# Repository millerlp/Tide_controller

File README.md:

Tide_controller
===============

Arduino code and associated files for building an aquarium tide height controller. This assumes that you 
have downloaded and installed the latest version of the Arduino software (v1.6.4, or newer).

Installation:

To operate the tide controller rack, install the following:

1. Install a copy of RTClib in your Arduino/libraries/ directory. If there is not already a libraries directory, create it now. RTClib can be downloaded from https://github.com/millerlp/RTClib. If the copy you download and unzip is called "RTClib-master", rename the folder to simply be "RTClib".

2. Copy the folder with the tide library for your site (i.e. TidelibSanDiegoSanDiegoBay) into Arduino/libraries/

3. Copy the Tide_controller_v2_5 folder (or most recent version) into your Arduino folder where 
your other sketches are normally stored. 

4. Open the Tide_controller sketch in the Arduino IDE, and make sure the correct tide site
library is referenced in the Initial Setup section, near line 57, with a line like:

	\#include "TidelibSanDiegoSanDiegoBay.h"

That line should contain the name of the library for your local site that you copied into Arduino/libraries/.

5. If you want to change the tide range in which the tide rack travels, you can change the
value for the upperPos on or around line 64, which looks like:
	float upperPos = 5.0;
That line represents the upper limit at which the tide rack will stop moving upward, even
if the predicted tide goes higher. The units of upperPos are feet (not meters or inches). 

Plug the Arduino in to the computer using a USB cable. Upload the program to the Arduino. 
Open the serial monitor to view the output. See the http://arduino.cc site for help with 
these steps. 

------------------------------
If the real time clock attached to the Arduino is not yet set, you need to set it one time
before loading the tide prediction software onto the Arduino. Open the Arduino software and 
go to File>Examples>RTClib>settime_exact.ino. Follow the instructions at the top of
that sketch to upload the correct time to your real time clock. Make sure the time you enter
is in your local standard time, not Daylight Savings Time (which runs Mar-Nov
in most places). The tide prediction routine relies on the time being set to local 
standard time for your site, otherwise you won't get the current tide height out. After running
the settime_exact.ino sketch, before unplugging the Arduino, immediately upload a different 
sketch (such as the Tide_controller sketch) to the Arduino so that the clock doesn't try to reset 
itself repeatedly when the Arduino restarts.

-------------------------------
If there is no folder containing a tide prediction library for your desired site, it
will be necessary to generate a library using the R scripts found in the 
Generate_new_site_libraries directory. The harmonic data for NOAA sites are all in
the Harmonics_20120302.Rdata file. With these data, you can generate a new library
by running the R script tide_harmonics_library_generator.R. Inside that file, you must
enter a name for the site you're interested in on the line
stationID = 'Monterey Harbor'
Change the value inside the quote marks to match your site, save the file, and run the
script in R. It will create a new directory with the necessary library files inside that
can be copied into the Arduino/libraries/ folder. Find the name for your site by looking 
through the XTide website http://www.flaterco.com/xtide/locations.html 
XTide only produces harmonics for 635 reference tide stations (all others are approximated 
from these tide stations), so you need to find the nearest station listed as "Ref" on that 
page, rather than "Sub" stations.

The other R scripts in the Generate_new_site_libraries directory could be used to make an
updated Rdata file when XTide updates the original harmonics database and after you
convert it to a text file using the libtcd library from the XTide site (see the notes inside
the R scripts).

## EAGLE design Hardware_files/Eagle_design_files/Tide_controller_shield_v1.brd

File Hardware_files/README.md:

Tide_controller/Hardware_files

A add-on 'shield' designed to be used with an Arduino Uno was designed for this
project. The shield provides mounting points for the real time clock (DS3231),
buttons, indicator LEDs, resistors, and connectors to interface with the stepper 
motor controller and displays. 

See the file 'Tide_shield_notes.pdf' for more information on how this shield
is meant to be wired and used.

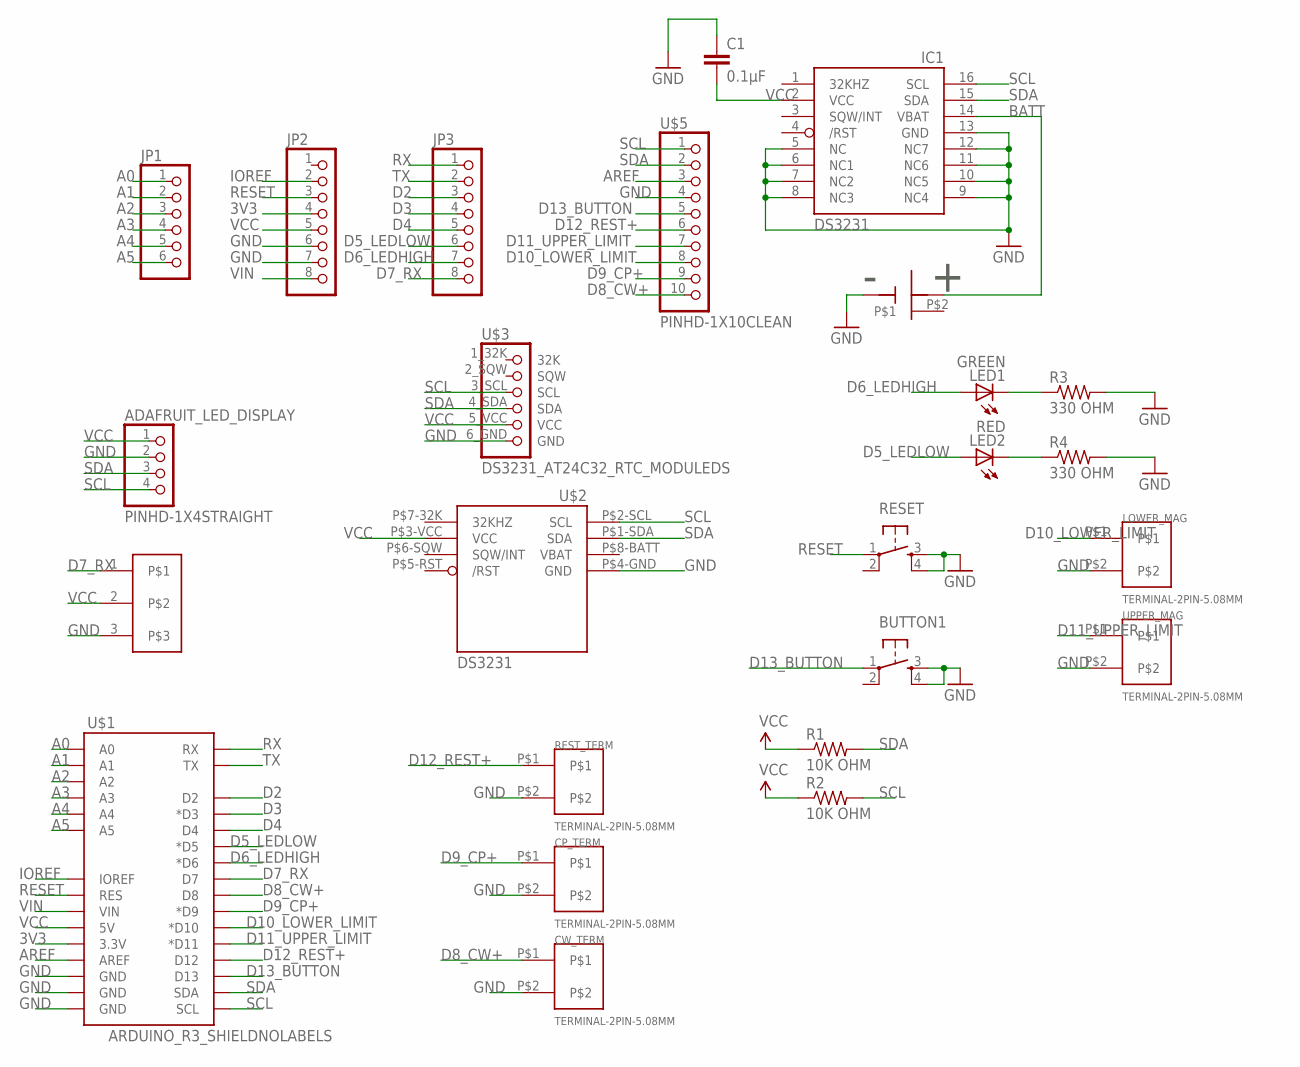
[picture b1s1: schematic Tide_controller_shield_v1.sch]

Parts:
ADAFRUIT_LED_DISPLAY: PINHD-1X4STRAIGHT; 1X04
BUTTON1: PUSHBUTTON-DPST-PTH; SWITCH-TACTILE-PTH-DPST
C1: 0.1µF; 0805
CP_TERM: TERMINAL-2PIN-5.08MM
CW_TERM: TERMINAL-2PIN-5.08MM
IC1: DS3231/SO; SO16W
JP1: PINHD-1X6CLEAN; 1X06-CLEAN
JP2, JP3: PINHD-1X8CLEANBIG; 1X08-CLEANBIG
LED1: GREEN; LED5MM
LED2: RED; LED5MM
LED_DISPLAY_SPARKFUN: PINHD-1X3; 1X03
LOWER_MAG: TERMINAL-2PIN-5.08MM
R1, R2: 10K OHM; 0309/10
R3, R4: 330 OHM; 0309/10
RESET: PUSHBUTTON-DPST-PTH; SWITCH-TACTILE-PTH-DPST
REST_TERM: TERMINAL-2PIN-5.08MM
U$1: ARDUINO_R3_SHIELDNOLABELS; UNO_R3_SHIELD_NOLABELS
U$2: CHRONODOT-OUTLINE
U$3: DS3231_AT24C32_RTC_MODULEDS; DS3231_AT24C32_RTC_MODULE
U$5: PINHD-1X10CLEAN; 1X10-CLEANBIG
U$6: CR1220_BATTERY_HOLDERSMD; CR1220_BATTERY_HOLDER_SMD
UPPER_MAG: TERMINAL-2PIN-5.08MM

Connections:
3V3: JP2.4, U$1.3.3V
A0: JP1.1, U$1.A0
A1: JP1.2, U$1.A1
A2: JP1.3, U$1.A2
A3: JP1.4, U$1.A3
A4: JP1.5, U$1.A4
A5: JP1.6, U$1.A5
AREF: U$1.AREF, U$5.3
BATT: IC1.14 (VBAT), U$6.P$1 (VBAT)
D2: JP3.3, U$1.D2
D3: JP3.4, U$1.D3 (*D3)
D4: JP3.5, U$1.D4
D5_LEDLOW: JP3.6, LED2.A, U$1.D5 (*D5)
D6_LEDHIGH: JP3.7, LED1.A, U$1.D6 (*D6)
D7_RX: JP3.8, LED_DISPLAY_SPARKFUN.1, U$1.D7
D8_CW+: CW_TERM.P$1, U$1.D8, U$5.10
D9_CP+: CP_TERM.P$1, U$1.D9 (*D9), U$5.9
D10_LOWER_LIMIT: LOWER_MAG.P$1, U$1.D10 (*D10), U$5.8
D11_UPPER_LIMIT: U$1.D11 (*D11), U$5.7, UPPER_MAG.P$1
D12_REST+: REST_TERM.P$1, U$1.D12, U$5.6
D13_BUTTON: BUTTON1.1, U$1.D13, U$5.5
GND: ADAFRUIT_LED_DISPLAY.2, BUTTON1.3, BUTTON1.4, C1.1, CP_TERM.P$2, CW_TERM.P$2, IC1.5 (NC), IC1.6 (NC1), IC1.7 (NC2), IC1.8 (NC3), IC1.9 (NC4), IC1.10 (NC5), IC1.11 (NC6), IC1.12 (NC7), IC1.13 (GND), JP2.6, JP2.7, LED_DISPLAY_SPARKFUN.3, LOWER_MAG.P$2, R3.2, R4.2, RESET.3, RESET.4, REST_TERM.P$2, U$1.GND@0 (GND), U$1.GND@1 (GND), U$1.GND@2 (GND), U$2.P$4-GND (GND), U$3.6_GND (GND), U$5.4, U$6.GND, UPPER_MAG.P$2
IOREF: JP2.2, U$1.IOREF
unnamed: LED1.K (C), R3.1
unnamed: LED2.K (C), R4.1
RESET: JP2.3, RESET.1, U$1.RES
RX: JP3.1, U$1.RX
SCL: ADAFRUIT_LED_DISPLAY.4, IC1.16 (SCL), R2.2, U$1.SCL, U$2.P$2-SCL (SCL), U$3.3_SCL (SCL), U$5.1
SDA: ADAFRUIT_LED_DISPLAY.3, IC1.15 (SDA), R1.2, U$1.SDA, U$2.P$1-SDA (SDA), U$3.4_SDA (SDA), U$5.2
TX: JP3.2, U$1.TX
VBAT: U$2.P$8-BATT (VBAT)
VCC: ADAFRUIT_LED_DISPLAY.1, C1.2, IC1.2 (VCC), JP2.5, LED_DISPLAY_SPARKFUN.2, R1.1, R2.1, U$1.5V, U$2.P$3-VCC (VCC), U$3.5_VCC (VCC)
VIN: JP2.8, U$1.VIN

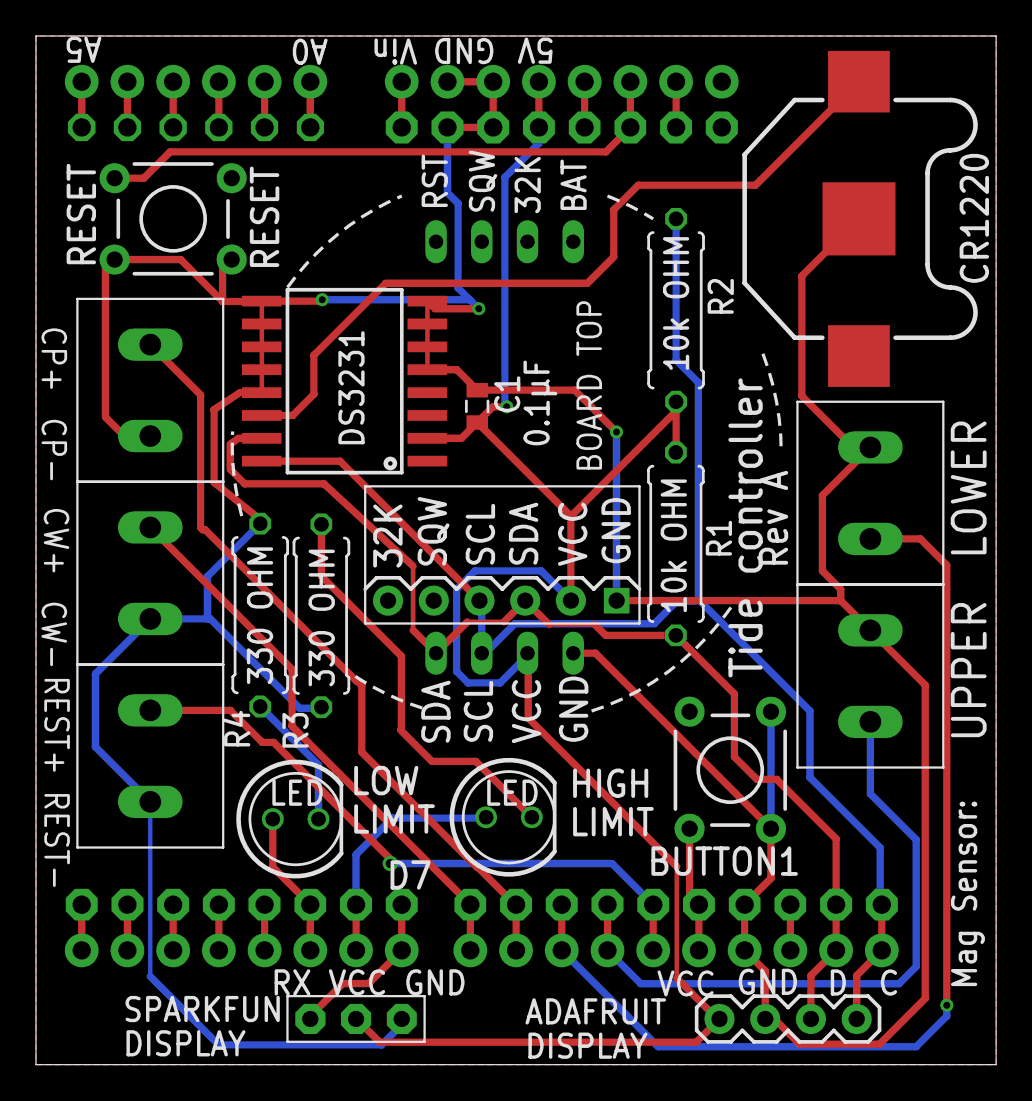
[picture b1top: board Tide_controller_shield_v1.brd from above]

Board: 2 copper layers, 53.3 x 57.1 mm, 25 parts (0 on the bottom side), 32 nets.

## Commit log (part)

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2012-05-03 Initial commit. Getting repository set up."
2012-05-03 GPL V3 license for the programs in this repository.
2012-05-03 This script contains two R functions for parsing a harmonics file from XTide.
2012-05-03 A script to extract data for a single tide station from the harmonics data generated by the tide_harmonics_parse.R script. This script outputs code to the command line that can be copied and pasted i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
2012-05-04 Initial commit of the Rdata file that can be read by the R script tide_extract_1site_harmonics.R. This Rdata file contains harmonics constituents for 637 reference tide stations from the NOAA databas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
2012-05-04 Added code to remove current speed stations from the harmonics data to reduce potential ambiguities in finding tide stations by name, since this code is only focused on predicting tide heights, not c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
2012-05-04 Still moving things around
2012-05-04 Changed output to send code to a text file that can be copy/pasted into the Arduino sketch. This creates code to initialize the various tide prediction arrays needed in the Arduino sketch.
2012-05-07 Started adding real time clock code, got sidetracked and instead switched to Motor_encoder_scratch2.ino. Updated setup instructions at bottom, PololuQik.h must also be modified, and the original Soft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
2012-05-07 Added code to calculate current year and hours since the start of current year.
2012-05-07 Added code to calculate current tide height once per minute. Need to check that timezone stuff is working still.
2012-05-08 First branch attempt
2012-05-09 First commit on this branch, no changes to .ino file
2012-05-09 Fixed duplication of values
2012-05-09 Added integer version of R script for generating the harmonic constants C code that is pasted into the Arduino sketch.
2012-05-09 Re-instated the PololuQik and WheelEncoders libraries and initialization during setup. The sketch still predicts tides correctly. No motor actuation is enabled yet.
2012-05-09 More housekeeping, adding comments.
2012-05-10 Started adding in code to calculate height difference and move motor up or down. Need to finish adding code to keep track of minutes and only allow one move per minute.
2012-05-11 Moved motor shut-off command outside of pin change counting while loop, since I suspect the motor shut-off if statement might have be causing counts to be missed.
2012-05-20 Started v1.3 with external interrupts
    Began laying out v1.3 of the tide controller. The
    previous version 1.2 mostly works as a proof of
    concept, so I'm leaving it as-is.
2012-05-20 Added code attribution for interrupts
    Forgot to include the reference to the external interrupt
    code. Updated now.
2012-06-01 Created v1.4 to use stepper motor
    The older versions used a normal electric motor with encoder,
    but the encoder counting routines often missed counts, leading
    to errors in position. This version will use a stepper motor to
    try to improve the accuracy of movements.
2012-06-01 Inserting stepper motor setup
    Starting to include the pin assignments and comments
    for driving a stepper motor via the Big Easy Driver.
    Still need to implement the motor turning in the main
    loop and also adjust the distance conversion factor for
    converting steps into linear distance.
2012-06-03 Updated to Arduino IDE 1.0.1
    Sketch compiles fine under new version.
2012-06-04 Inserted code to return to home position
    Added a while loop in the setup loop to bring the sled
    position back to the home position at the upperLimitSwitch.
    This will run until the upperLimitSwitch is activated. This
    gives the program a constant starting position on each
    reboot.
2012-06-04 Implemented new logic tests for moving motor
    The decision to move the motor now relies on checking
    that the new target position is within both the lower
    and upper limits of the rack, and that the appropriate
    limit switch hasn't already been activated.
    Also modified the conversion factor for distance per
    motor step to work with the 10tpi lead screw.
2012-06-04 Added a single delay during setup loop.
2012-06-04 Adding comments, changed lower limit logic
    Changed the lower limit switch logic so that the last
    position stored when the lower limit switch activates is
    the actual distance traveled from the upper limit, not
    the hard-coded lower limit value (in lowerPos). This is
    because the magnetic switch position is often imprecise, so
    one of the two switch positions needs to be taken as
2012-06-04 Added some more debugging output to serial monitor
    Notifying user when the motor is at either of the
    travel limit switches.
2012-06-05 Added some formatting to debug output
2012-06-07 Moving all the tidal harmonic data to progmem
    This is a first attempt at storing the voluminous
    tidal harmonic constituents in program memory to
    hopefully fit more years worth of data on the
    microcontroller.
2012-06-07 Printing more digits in serial output
    Just added a digits format to the previous
    tide height serial output message.
2012-06-07 Cleaning out old obsolete files
2012-06-07 Added commentary at top
    Just explaining the limitations of the older
    versions of the code.
2012-06-07 Added comments at top of file
    No code changes.
2012-06-08 Cleaning up some old lines, added comment
    Turns out I wasn't using the seconds variable that I
    defined long ago. Added reference to the RTC library.
2012-06-08 Updated to newer progmem version of output.
2012-06-08 Updating more comments
    No code changes
2012-06-08 Switched harmonics to float values
    Trying to reduce the complexity of the code by
    removing the integer-conversion steps for the tidal
    harmonic constituents now that I no longer need to save
    the memory space. Tide output is still accurate.
2012-06-08 Updated tidal harmonics code
2012-06-08 Updated harmonics code generation script
    Changed the R script to output C code for the Arduino
    that keeps the harmonic constituents as float values
    to simplify the picture of what's going on.
2012-06-08 Removed superfluous comment
    No code changes
2012-06-08 Removing some old cruft
2012-06-08 Created readme file
2012-06-08 Inserted info for RTClib repository
    Since someone might want to download that library at
    some point in the future.
2012-06-10 Added .DS_Store to ignore list
2012-06-10 Tide calculation library for Port San Luis, CA
2012-06-10 Created keywords.txt file for keyword highlighting
2012-06-10 Moving old files out of main directory
    No code changes, just hiding old versions.
2012-06-10 R script for generating tide prediction libraries
    Use this script, along with the other R scripts in this
    directory, to generate tide prediction libraries for the
    site of your choice.
2012-06-10 Formatting issues
2012-06-11 Updated for new real time clock library
    Exposes more functionality of the DS3231 clock if needed,
    retains compatibility with the older DS1307 chip.
2012-06-11 Updated to new real time clock library
    Allows compatibility with newer DS3231 clock chip, including
    extra functionality. Maintains compatibility with the older
    DS1307 clock as well.
2012-06-11 Added copy of new real time clock library
2012-06-11 Updating for new arrangement.
2012-06-19 Created Los Angeles tide prediction library
    Use this library when you want to make tide predictions for
    Los Angeles, CA harbor and surrounding area. Place the
    TideLosAngeleslib folder (with all its contents) into your
    arduino-1.x.x/libraries/ folder.
    You must also insert the line:
    \#include = "TideLosAngelslib"
2012-07-06 Changed decimals of tide printout
2012-07-15 Added code for 7-segment display
    Updated pin assignments to work with new daughterboard
    design, and added function to display current tide
    height on a Sparkfun 4-digit 7-segment LED display.
2012-07-17 Changed tide height limits
2012-07-17 Implemented ENABLE line on stepper driver
    The Big Easy Driver has an enable line that can be used to
    shut down power to the stepper motor when pulled high.
    Because the lead-screw design of the rack holds position when
    the motor is powered off, I can use the enable line to shut
    down the motor between movements and thereby reduce the heat
    production of the Big Easy Driver and the motor. It has the
2012-07-17 Added some delays after enable commands
2012-07-26 Adjusted upper shore height test in movement code
    Needed to add a larger buffer to the upper tide height limit
    when moving the carriage upward, in case a heavy load causes
    some steps to be missed. This should allow the carriage to reach
    the upper limit switch and properly re-home itself.
2012-07-30 Update with stepperEnable, starting overrideButton
    Caught up with version 1.10 by including stepperEnable logic.
    Starting to implement an override button to drive motor carriage
    downward when needed.
2012-07-31 Fixed lower limit switch logic in override code
    Added some comments, enabled and tested the override code.
2012-07-31 Modified setup loop to move carriage to position
    The setup loop now has code to move the carriage to the
    current tide height after initially moving the carriage up to
    find home (upper limit). This avoids situations where the
    unit is powered up while the real tide is below the lower
    travel limit and the program would hang.
2012-07-31 Changed version number in comments.
2012-08-01 Updating instructions
2012-08-10 Adding helpful comments.
    Altered code for lowerPos so that it simply calculates the value
    based on the user's chosen upperPos value. There is a hard-coded
    value of 2.75 in there to represent the travel limits of the
    first tide control rack that I built. The goal is to simplify things
    so that the user only has to set one value (upperPos) if they want
    to alter the tide range that the tide rack covers.
2012-08-10 Clarifying once more.
2012-08-17 Moving things to other repositories
    Moved tide calculator sketch to its own repository
2012-09-08 Updated with new reference to library
    The library naming convention just changed, so the call to the
    tide prediction library has been updated to address the new situation.
2012-09-08 Fixing typo in generated site library
2013-01-25 New version. Adding more serial output for now, will eventually turn off microstepping mode.
2013-01-26 Updated installation instructions
2013-02-02 New version that allows you to choose between full-step mode and microstepping mode, provided the revision 7 daughterboard is being used. Otherwise, you can only use the microstepping mode
2013-05-16 Added some comments
2013-05-30 Updating comments to reflect the wiring on the new interface board and new stepper motor driver hardware.
2013-05-30 Updated to cover 2013 through 2036.
2014-05-27 Updated with new comments and info on dip switch settings for 1/16th microstepping mode.
2014-12-12 Added real time clock set + read sketches contributed by Robert Lozyniak.
2015-03-20 Code for new 2ft travel version, where upper limit sensor has been moved down the rack rail to sit 2.0ft (24inches) above the lower limit sensor. Tide height has been set so that the upper limit corr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
2015-03-27 Updated tide generating script to produce libraries that work with the newest version of the Arduino IDE v1.6.1
2015-05-20 Fixed the sevenSegDisplayTime function to properly read the hour, minutes values
2015-05-28 Updating the RTClib reference and link.
2015-05-28 Fixing typo
2015-05-28 Changing reference to RTClib location
2015-06-18 Updated to grab site numbers
2015-06-18 Moved old versions to the old_version directory
2015-08-30 Updated 7-segment LED sparkfun display code to show more output during each new minute. Changed the declaration of the limit switches to use INPUT_PULLUP option, more in line with modern Arduino synt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
2022-02-18 Fix image link
2022-06-08 Updated Eagle version
2026-02-11 Updating with tide library to run through 2045
